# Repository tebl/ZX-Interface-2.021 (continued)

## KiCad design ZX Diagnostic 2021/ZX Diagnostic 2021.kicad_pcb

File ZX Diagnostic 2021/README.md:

# ZX Diagnostic 2.021
The *ZX Diagnostic 2.021*, simply referred to as the *diagnostic cartridge* for the remainder of this document, has been specially made to work with the [diagnostic firmware](https://github.com/brendanalford/zx-diagnostics) developed by Brendan Alford. Part of the hardware used within the *ZX Interface 2.021* has been designed to be functionally similar to other diagnostic cartridges, in particular the bank switching scheme and the way  the cartridge can be disabled by the computer was based on the following [blog post](https://blog.gjmccarthy.co.uk/wp-content/uploads/2019/12/how.html).

The rest of the functionality needed to serve as a diagnostic cartridge has been added to the *ZX Diagnostic 2.021*, apart from being a 16K cartridge there is an 8bit latch that will be used to output diagnostic status to the LEDs. The LEDs will allow some additional feedback to show that the computer is somewhat functional, even when there there is no image. Compared to the *ZX Cartridge 2.021*, this only supports a single ROM chip with sizes ranging ranging from 27C128 up to 27C512.

Note that there are various faceplates available for the cartridges, these complete the look of the cartridge as well as help them balance on top of the interface. Check out the [faceplates](https://github.com/tebl/ZX-Interface-2.021/tree/main/faceplates) section for an overview over the ones that have been made available, also see [PCBWay shared projects](https://www.pcbway.com/project/shareproject/?tag=ZX%20Interface%202.021).

- [1> Building the cartridge](#1-building-the-cartridge)
  - [1.1> Soldering it together](#11-soldering-it-together)
  - [1.2> Assembling the unit](#12-assembling-the-unit)
  - [1.3> Testing it out](#13-testing-it-out)
- [2> Schematic](#2-schematic)
- [3> BOM](#3-bom)

# 1> Building the cartridge
Building the unit assumes you have at least minor experience soldering things together, recommended is at least a soldering station with adjustable temperature to get started - usually you'll want some 60/40 solder tin (if you can get that where you live). Given that we're going to be flashing data onto EPROM chips, you'll need an EPROM programmer suitable for this task - the one I'm using is a MiniPro TL866CS and so far it's surpassed my expectations for such a reasonably priced device. If you are going to use EPROM chips you will need an EPROM ereaser as well, but read on - you might not need that depending on the chips you purchase.

With the equipment sorted, now comes the shopping - so head on over to the [BOM](#3-bom)-section for some information on what you need. Note that with sites such as ebay, AliExpress and similar sites that sell cheap chinese components, you'll need to treat these as a suggested search term and look for something that matches the gallery pictures.

You'll need to order some EPROM chips as well. As previously mentioned, you can use anything from 27C128 up to 27C512 chips. One specific chip I can recommend looking for is the W27C512 chip as that is actually an EEPROM with the same pin layout, meaning you won't need the previously mentioned EPROM ereaser. The price difference is negligible unless you're going to make a lot of them.

## 1.1> Soldering it together
The construction of this unit should be fairly straight-forward, just take your time in order to make sure everything goes into place - more or less straight. I usually recommend starting by having a good look at the PCBs, try to figure out where all of the listed components go and in which orientation they go (all of this should be clearly marked on the silkscreen). 

The last version I built is the one shown above, and going forward I usually try installing components sorted by physical - going from the smallest to the largest. The reason for this is that you want to be able to solder most of it into place before it starts wobbling on your desk, for the *ZX Diagnostic 2.021* this means saving all of those LEDs until last.

At this point we've soldered in all of the resistors, but take note that one of them will have a different resistor value from the others. There are two solder jumpers on the cartridge, these are clearly labelled A14 and A15 with pin 1 identifiable as the square pad. You need to add some solder to bridge between two of the pins, this is dependent on the type of (E)EPROM you are going to install into the socket marked U1 - see the table below for all supported ROM types.

| (E)EPROM | A15 | A14 |
| -------- | --- | --- |
| 27C512   | 1-2 | 1-2 |     
| 27C256   | 2-3 | 1-2 |     
| 27C128   | 2-3 | 2-3 |

Next is the single right-angle pin header that is used to enable the LEDs at the top - to get that on straight, just solder on one of the pins, then reheat and adjust the position before soldering in the final pin. Alternatively you could also just solder a wire across the two pins to keep them permanently disabled, but this isn't recommended unless you know that the cartridge will only ever be used for diagnostic purposes.

At this point, we've just gone ahead and added both the sockets, making sure to match the indent in the sockets with the symbols on the silkscreen - this means that pin 1 of the ICs is at the top-right corner of the sockets. Solder in the corners of the sockets first, gently reheat one pin at a time and press the socket firmly against board to avoid accidentally soldering it in at an angle (removing a socket is a lot harder than it is to solder it in).

The ceramic capacitors do not have a polarity, so we can just solder them into place without issues. Personally I tend to ensure that the values printed on them is visible from the outside, but that's just nit-picking.

The last thing we're going to solder into place is the LEDs, but as they need to line up with the holes in the faceplate we'll need to take care when doing so to ensure that they're straight. Before we get that far though, we'll need to say a few words about the LEDs themselves - soldering them in the wrong way will ensure that won't work. I can never remember what the proper names of each of the pins are, so I'll just pass along the way I do it - essentially the longest lead goes into the round hole. The shorter lead, big surprise here, goes into the other hole.

Just do one row at a time, soldering in just one of the pins - then reheat and push the LED flush against the board (no matter how hard I try, they're never straight enough on the first try). When you're sure that all of them line up correctly, only then do you solder in the other pin.

The last step that we need to do is simply inserting the chips, as has been pictured so far I've soldered the jumpers according to the settings for a 27C512-type of ROM - in this case using the W27C512 EEPROM. Make sure that you insert the chips in the correct orientation, the indent will be to the right. I put together a separate document that goes into [flashing the (E)EROMs](https://github.com/tebl/ZX-Interface-2.021/blob/main/documentation/flash_eeprom.md), the diagnostic firmware can be downloaded from the authors [github](https://github.com/brendanalford/zx-diagnostics/releases)-repository (it'll be called *testrom.bin*, this file can only be downloaded as part of the releases). Then add a jumper cap to enable the LEDs.

## 1.2> Assembling the unit
There isn't all that much that can be said for assembling the unit, chances are you've already finished the entire thing by this point. The only remaining step would just be to add a [faceplate](https://github.com/tebl/ZX-Interface-2.021/tree/main/faceplates), it helps keep the cartridge from flopping around in the cartridge slot while also adding quite a bit of visual flair to it.

The faceplate is just a simple PCB, the suggested way of attaching it is by using components found in cheap *M3 nylon hex* kits. It will look at its best when using an 8mm nylon hex standoff (F-F), then adding screws from both sides. If, on the other hand, you want to stay within the kit - then I suggest using the 8mm M-F standoffs, add M3 nuts on the bottom and snip off the remaining part of the nylon screw that'll poke through. Add screws on top. Your success on this step will be dependent on how straight you soldered on the LEDs, so reheat and adjust any that fails to line up with the holes in the faceplate.

## 1.3> Testing it out
I shouldn't have to say it at this point, but I'll do so anyway - cartridges are not memory cards, plugging them in or unplugging them while the system is powered on will **KILL** your equipment. With that out of the way, just plug the cartridge into the slot and then apply power to see if whatever you put into the first 16K of the (E)EPROM starts up as expected. I put together a separate document that goes into [flashing the (E)EROMs](https://github.com/tebl/ZX-Interface-2.021/blob/main/documentation/flash_eeprom.md).

The ZX Spectrum doesn't actually have any knowledge of any of the bank switching logic installed on the interface, in fact the ROM in your computer will be completely disabled when any cartridge is inserted into the interface. Given that this is meant to be a diagnostic cartridge, I'll assume you've gone ahead and used Brendan Alfords diagnostic firmware as the first 16K bank - it should start automatically and run through the tests as it should.

Unless you hold down any of the buttons when starting the computer, it should run through all of the tests once and then - after a countdown - page out the diagnostic ROM and return you to the standard ZX Spectrums basic. This is normal, it just shows that the entire system for the most part works as it should. At this point you might want to try out any of the images put into the other ROM banks, I've added some more details on what to do next to the [bank_switching](https://github.com/tebl/ZX-Interface-2.021/blob/main/documentation/bank_switching.md) document.

You can control the LEDs directly from basic if you want to, they're placed on port 63 and by using the *OUT* command you can control them. All you need to do is write a value to have the LEDs display it in binary, for example the following to separately light up each row of LEDs:
```
OUT 63, 85
OUT 63, 170
```

You know you want to program an LED chaser now, you know you do! In case you're not old enough, they're what made KITT cool and the Cylons scary.

# 2> Schematic
The supplied KiCad files should be sufficient as both a schematic and as a  starting point for ordering PCBs (basically you could just zip the contents of the export folder and upload that on a fabrication site), the schematic is also available in [PDF-format](https://github.com/tebl/ZX-Interface-2.021/tree/main/documentation/schematic) and this is what you'll need to print and work your way through this things don't work as expected after assembly.

# 3> BOM
Most parts should be easy to get a hold of from your favourite local electronic component shop, but given that I don't have access to such shops where I live so everything was based on whatever I could get cheapest from eBay/AliExpress (free shipping, but plan on waiting 3-4 weeks for delivery). Components in parenthesis can be considered optional to enable basic functionality, but where's the fun in that? You deserve the complete package.

| Reference             | Item                                                              | Count | Order  |
| --------------------- | ----------------------------------------------------------------- | ----- | ------ |
| Cartridge PCB         | Fabricate using Gerber files                                      |     1 | [PCBWay](https://www.pcbway.com/project/shareproject/ZX_Diagnostic_2_021.html)
| Faceplate PCB *       | Fabricate using Gerber files                                      |    (1)| [PCBWay](https://www.pcbway.com/project/shareproject/ZX_Diagnostic_2_021__Faceplate_FA1_.html)
| JP1 **                | 2pin right-angle pin-header (with jumper cap)                     |    (1)|
| U1                    | 27C128,27C256 or 27C512 (W27C512 recommended)                     |     1 |
| U2 **                 | 74HCT374 (DIP-20)                                                 |    (1)|
| C1                    | 100nF ceramic capacitor (5mm pin spacing)                         |     1 |
| C2 **                 | 100nF ceramic capacitor (5mm pin spacing)                         |    (1)|
| R1-R8 **              | 330 ohm resistor                                                  |    (8)|
| R9 **                 | 10k ohm resistor                                                  |     1 |
| Mounting *            | Nylon M3 hex standoffs 8mm                                        |    (4)|
| Mounting *            | Nylon M3x6mm nylon screws                                         |    (4)|
| Mounting *            | M3 nylon nut                                                      |    (4)|  

*) The easiest way of ordering these is to just one of the M3 nylon standoff kits on ebay, AliExpress or any similar sites. That way you'll get more than what you need in various sizes for future projects as well. Check out [faceplate](https://github.com/tebl/ZX-Interface-2.021/tree/main/faceplates) section of this repository or [PCBWay shared projects](https://www.pcbway.com/project/shareproject/?tag=ZX%20Interface%202.021) for available options.

**) These components are used for the LED output, they can be considered optional for building a simple cartridge though they're recommended when you want to use it for diagnostic purposes.

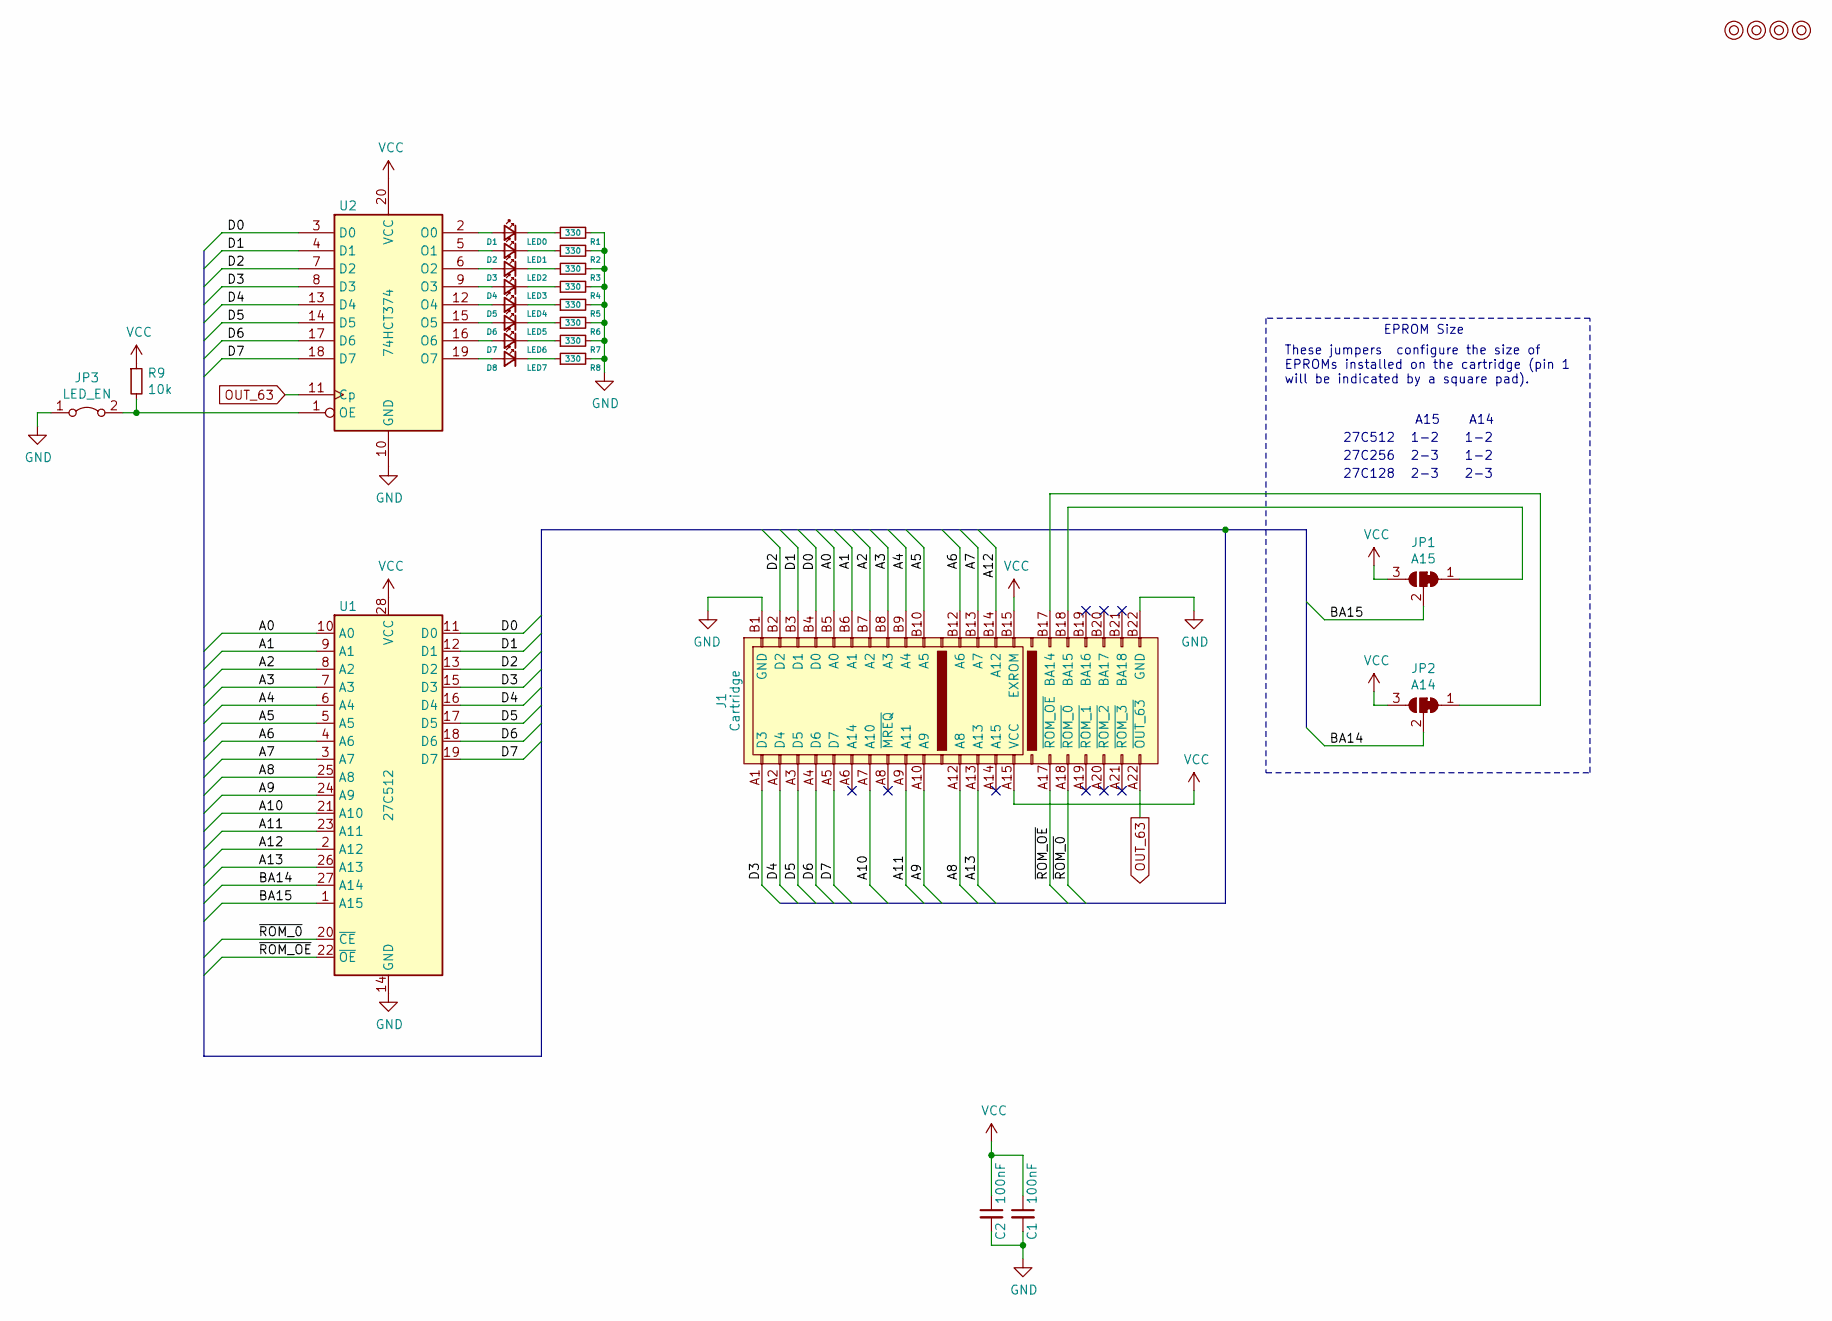
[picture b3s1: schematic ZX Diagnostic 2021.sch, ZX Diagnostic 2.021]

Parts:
C1, C2: 100nF; C_Disc_D4.7mm_W2.5mm_P5.00mm
D1: LED0; LED_D5.0mm
D2: LED1; LED_D5.0mm
D3: LED2; LED_D5.0mm
D4: LED3; LED_D5.0mm
D5: LED4; LED_D5.0mm
D6: LED5; LED_D5.0mm
D7: LED6; LED_D5.0mm
D8: LED7; LED_D5.0mm
J1: Cartridge; ZX_Spectrum_Cartridge
JP1: A15; select
JP2: A14; select
JP3: LED_EN; PinHeader_1x02_P2.54mm_Horizontal
M1, M2, M3, M4: Mounting; M3_pin
R1, R2, R3, R4, R5, R6, R7, R8: 330; R_Axial_DIN0207_L6.3mm_D2.5mm_P10.16mm_Horizontal
R9: 10k; R_Axial_DIN0207_L6.3mm_D2.5mm_P10.16mm_Horizontal
U1: 27C512; DIP-28_W15.24mm_Socket_LongPads
U2: 74HCT374; DIP-20_W7.62mm_Socket_LongPads

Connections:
/A0: J1.B5 (A0), U1.10 (A0)
/A1: J1.B6 (A1), U1.9 (A1)
/A2: J1.B7 (A2), U1.8 (A2)
/A3: J1.B8 (A3), U1.7 (A3)
/A4: J1.B9 (A4), U1.6 (A4)
/A5: J1.B10 (A5), U1.5 (A5)
/A6: J1.B12 (A6), U1.4 (A6)
/A7: J1.B13 (A7), U1.3 (A7)
/A8: J1.A12 (A8), U1.25 (A8)
/A9: J1.A10 (A9), U1.24 (A9)
/A10: J1.A7 (A10), U1.21 (A10)
/A11: J1.A9 (A11), U1.23 (A11)
/A12: J1.B14 (A12), U1.2 (A12)
/A13: J1.A13, U1.26 (A13)
/BA14: JP2.2 (C), U1.27 (A14)
/BA15: JP1.2 (C), U1.1 (A15)
/D0: J1.B4 (D0), U1.11 (D0), U2.3 (D0)
/D1: J1.B3 (D1), U1.12 (D1), U2.4 (D1)
/D2: J1.B2 (D2), U1.13 (D2), U2.7 (D2)
/D3: J1.A1 (D3), U1.15 (D3), U2.8 (D3)
/D4: J1.A2 (D4), U1.16 (D4), U2.13 (D4)
/D5: J1.A3 (D5), U1.17 (D5), U2.14 (D5)
/D6: J1.A4 (D6), U1.18 (D6), U2.17 (D6)
/D7: J1.A5 (D7), U1.19 (D7), U2.18 (D7)
/~ROM_0: J1.A18 (~ROM_0), U1.20 (~CE)
/~ROM_OE: J1.A17 (~ROM_OE), U1.22 (~OE)
GND: C1.2, C2.2, J1.B1 (GND), J1.B22 (GND), JP3.1 (A), R1.2, R2.2, R3.2, R4.2, R5.2, R6.2, R7.2, R8.2, U1.14 (GND), U2.10 (GND)
unnamed: D1.1 (K), R1.1
unnamed: D1.2 (A), U2.2 (O0)
unnamed: D2.1 (K), R2.1
unnamed: D2.2 (A), U2.5 (O1)
unnamed: D3.1 (K), R3.1
unnamed: D3.2 (A), U2.6 (O2)
unnamed: D4.1 (K), R4.1
unnamed: D4.2 (A), U2.9 (O3)
unnamed: D5.1 (K), R5.1
unnamed: D5.2 (A), U2.12 (O4)
unnamed: D6.1 (K), R6.1
unnamed: D6.2 (A), U2.15 (O5)
unnamed: D7.1 (K), R7.1
unnamed: D7.2 (A), U2.16 (O6)
unnamed: D8.1 (K), R8.1
unnamed: D8.2 (A), U2.19 (O7)
unnamed: J1.B17 (BA14), JP2.1 (A)
unnamed: J1.B18 (BA15), JP1.1 (A)
unnamed: JP3.2 (B), R9.2, U2.1 (OE)
OUT_63: J1.A22 (~OUT_63), U2.11 (Cp)
VCC: C1.1, C2.1, J1.A15 (VCC), J1.B15 (EXROM), JP1.3 (B), JP2.3 (B), R9.1, U1.28 (VCC), U2.20 (VCC)

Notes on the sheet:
EPROM Size
These jumpers configure the size of EPROMs installed on the cartridge (pin 1 will be indicated by a square pad).
A15
A14
27C512
27C256
27C128
1-2
2-3

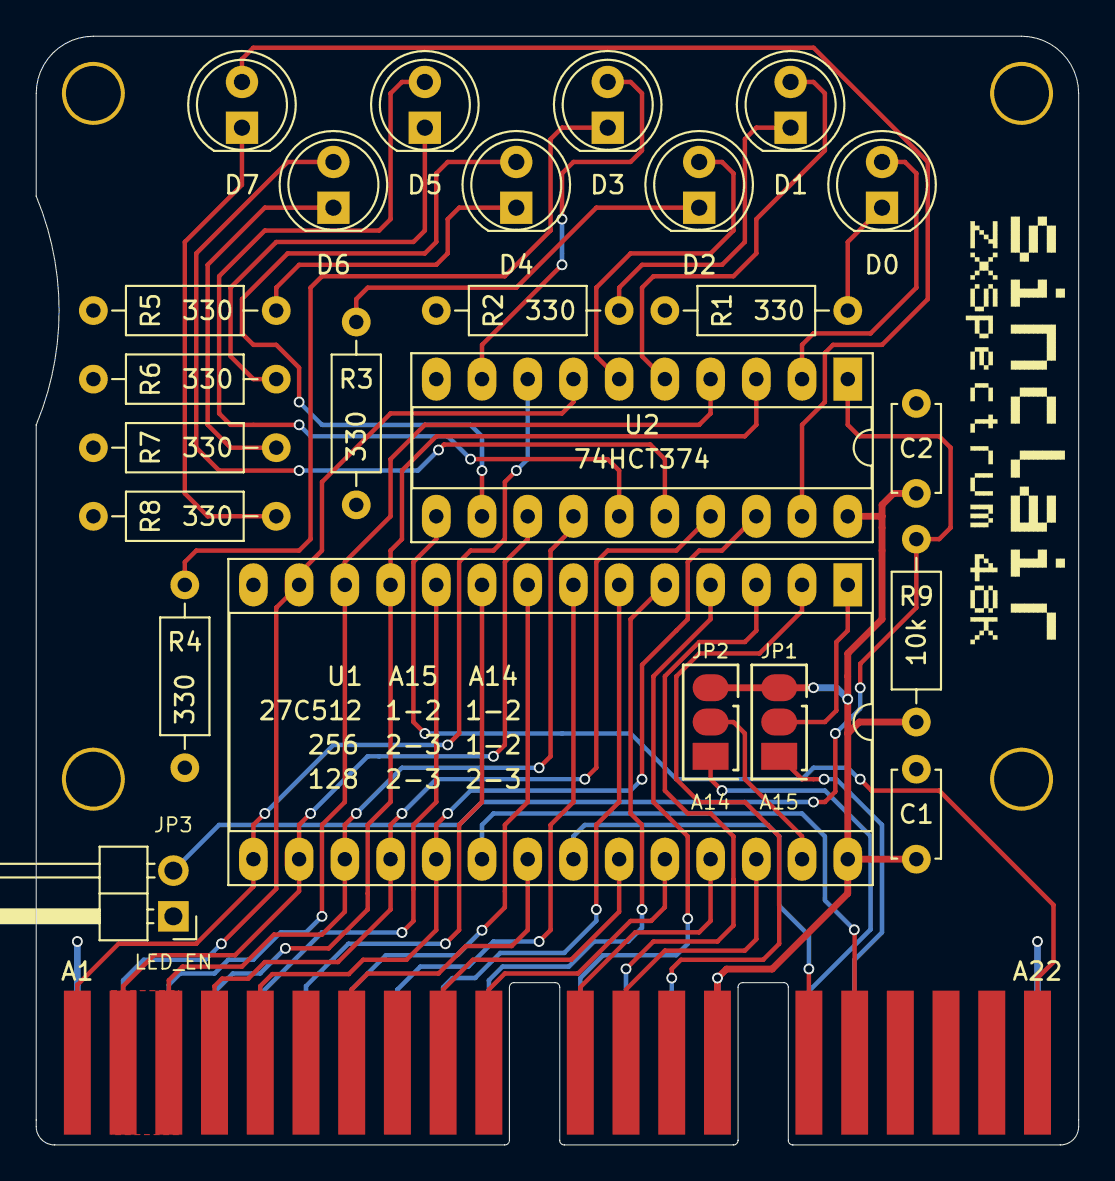
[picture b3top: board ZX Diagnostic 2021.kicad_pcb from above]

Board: 2 copper layers, 57.9 x 61.6 mm, 30 parts (0 on the bottom side), 48 nets.

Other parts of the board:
sinclair_title: sinclair_title

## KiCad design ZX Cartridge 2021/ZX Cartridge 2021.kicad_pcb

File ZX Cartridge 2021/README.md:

# ZX Cartridge 2.021
The ZX Cartridge 2.021, simply referred to as *cartridge* for the remainder of this document, is a modified version of the one released by Sinclair back in 1983. The original cartridge design was limited to 16K without any of the signals required to easily build a larger one, so the *ZX Cartridge 2.01* set out to fix that - simply by extending the length of the cartridge. This does mean that you can't use it with the original *Sinclair ZX Interface 2*, you can only use it with the *ZX Interface 2.021*.

Though the interface itself is able to address ROM chips in sizes up to 512K, four of them actually, the cartridge itself was designed with the ROM chips ranging from 27C128 up to 27C512. I might make a monster cartridge at some point, but given that there were only around 10 cartridges released for the original system - having the space for 8 of them is a good starting point.

Note that there are various faceplates available for the cartridges, these complete the look of the cartridge as well as help them balance on top of the interface. Check out the [faceplates](https://github.com/tebl/ZX-Interface-2.021/tree/main/faceplates) section for an overview over the ones that have been made available, also see [PCBWay shared projects](https://www.pcbway.com/project/shareproject/?tag=ZX%20Interface%202.021).

- [1> Building the cartridge](#1-building-the-cartridge)
  - [1.1> Soldering it together](#11-soldering-it-together)
  - [1.2> Assembling the unit](#12-assembling-the-unit)
  - [1.3> Testing it out](#13-testing-it-out)
- [2> Schematic](#2-schematic)
- [3> BOM](#3-bom)

# 1> Building the cartridge
Building the unit assumes you have at least minor experience soldering things together, recommended is at least a soldering station with adjustable temperature to get started - usually you'll want some 60/40 solder tin (if you can get that where you live). Given that we're going to be flashing data onto EPROM chips, you'll need an EPROM programmer suitable for this task - the one I'm using is a MiniPro TL866CS and so far it's surpassed my expectations for such a reasonably priced device. If you are going to use EPROM chips you will need an EPROM ereaser as well, but read on - you might not need that depending on the chips you purchase.

With the equipment sorted, now comes the shopping - so head on over to the [BOM](#3-bom)-section for some information on what you need. Note that with sites such as ebay, AliExpress and similar sites that sell cheap chinese components, you'll need to treat these as a suggested search term and look for something that matches the gallery pictures.

You'll need to order some EPROM chips as well. As previously mentioned, you can use anything from 27C128 up to 27C512 chips. One specific chip I can recommend looking for is the W27C512 chip as that is actually an EEPROM with the same pin layout, meaning you won't need the previously mentioned EPROM ereaser. The price difference is negligible unless you're going to make a lot of them.

## 1.1> Soldering it together
The construction of this unit should be straight-forward, specifically as there are only a handful of components to deal with. If you are only going to install a single (E)EPROM into the board, you just need to solder in the left socket and the capacitor next to it.

There are two solder jumpers on the right side of the cartridge, these are clearly labelled A14 and A15 with pin 1 identifiable as the square pad. You need to add some solder to bridge between two of the pins, this is dependent on the type of (E)EPROM you are going to install into the slots (they need to be of the same kind so no mixing and matching).

| (E)EPROM | A15 | A14 |
| -------- | --- | --- |
| 27C512   | 1-2 | 1-2 |     
| 27C256   | 2-3 | 1-2 |     
| 27C128   | 2-3 | 2-3 |     

A completed unit with the jumpers soldered in for the installed 27C512 chip can be seen below, this is mainly all there is to it. The rest of the components that are usually associated with ZX Spectrum cartridges are integrated into the *ZX Interface 2.021* instead - meaning you can quickly solder together all the cartridges you'll ever need in just a few minutes.

## 1.2> Assembling the unit
There isn't all that much that can be said for assembling the unit, chances are you've already finished the entire thing by this point. The only remaining step would just be to add a [faceplate](https://github.com/tebl/ZX-Interface-2.021/tree/main/faceplates), it helps keep the cartridge from flopping around in the cartridge slot while adding quite a bit of visual flair to it.

The faceplate is just a simple PCB, the suggested way of attaching it is by using components found in cheap *M3 nylon hex* kits. It will look at its best when using an 8mm nylon hex standoff (F-F), then adding screws from both sides. If, on the other hand, you want to stay within the kit - then I suggest using the 8mm M-F standoffs, add M3 nuts on the bottom and snip off the remaining part of the nylon screw that'll poke through. Add screws on top.

## 1.3> Testing it out
I shouldn't have to say it at this point, but I'll do so anyway - cartridges are not memory cards, plugging them in or unplugging them while the system is powered on will **KILL** your equipment. With that out of the way, just plug the cartridge into the slot and then apply power to see if whatever you put into the first 16K of the (E)EPROM starts up as expected.

The ZX Spectrum doesn't actually have any knowledge of any of the bank switching logic installed on the interface, in fact the ROM in your computer will be completely disabled when any cartridge is inserted into the interface. So in order to access any of the other banks available we'll need to come up with something else, but that is described separately in [bank_switching](https://github.com/tebl/ZX-Interface-2.021/blob/main/documentation/bank_switching.md) that have been included as part of the [documentation](https://github.com/tebl/ZX-Interface-2.021/tree/main/documentation).

# 2> Schematic
The supplied KiCad files should be sufficient as both a schematic and as a  starting point for ordering PCBs (basically you could just zip the contents of the export folder and upload that on a fabrication site), the schematic is also available in [PDF-format](https://github.com/tebl/ZX-Interface-2.021/tree/main/documentation/schematic) and this is what you'll need to print and work your way through this things don't work as expected after assembly.

# 3> BOM
Most parts should be easy to get a hold of from your favourite local electronic component shop, but given that I don't have access to such shops where I live so everything was based on whatever I could get cheapest from eBay/AliExpress (free shipping, but plan on waiting 3-4 weeks for delivery). 

| Reference             | Item                                                              | Count | Order  |
| --------------------- | ----------------------------------------------------------------- | ----- | ------ |
| Cartridge PCB         | Fabricate using Gerber files                                      |     1 | [PCBWay](https://www.pcbway.com/project/shareproject/ZX_Cartridge_2_021.html)
| Faceplate PCB *       | Fabricate using Gerber files                                      |    (1)| [PCBWay](https://www.pcbway.com/project/shareproject/ZX_Cartridge_2_021__Faceplate_FA1_.html)
| U1,U2 **              | 27C128,27C256 or 27C512 (W27C512 recommended)                     |  1 (1)|
| C1,C2 **              | 100nF ceramic capacitor (5mm pin spacing)                         |  1 (1)|
| Mounting *            | Nylon M3 hex standoffs 8mm                                        |    (4)|
| Mounting *            | Nylon M3x6mm nylon screws                                         |    (4)|
| Mounting *            | M3 nylon nut                                                      |    (4)|  

*) The easiest way of ordering these is to just one of the M3 nylon standoff kits on ebay, AliExpress or any similar sites. That way you'll get more than what you need in various sizes for future projects as well. Check out [faceplate](https://github.com/tebl/ZX-Interface-2.021/tree/main/faceplates) section of this repository or [PCBWay shared projects](https://www.pcbway.com/project/shareproject/?tag=ZX%20Interface%202.021) for available options.

**) Only a single (E)EPROM is required to build a cartridge, components U2 and C2 are therefore listed as optional. Installing 28-pin wide DIP sockets is highly recommended rather than soldering the (E)EPROM directly to the board.

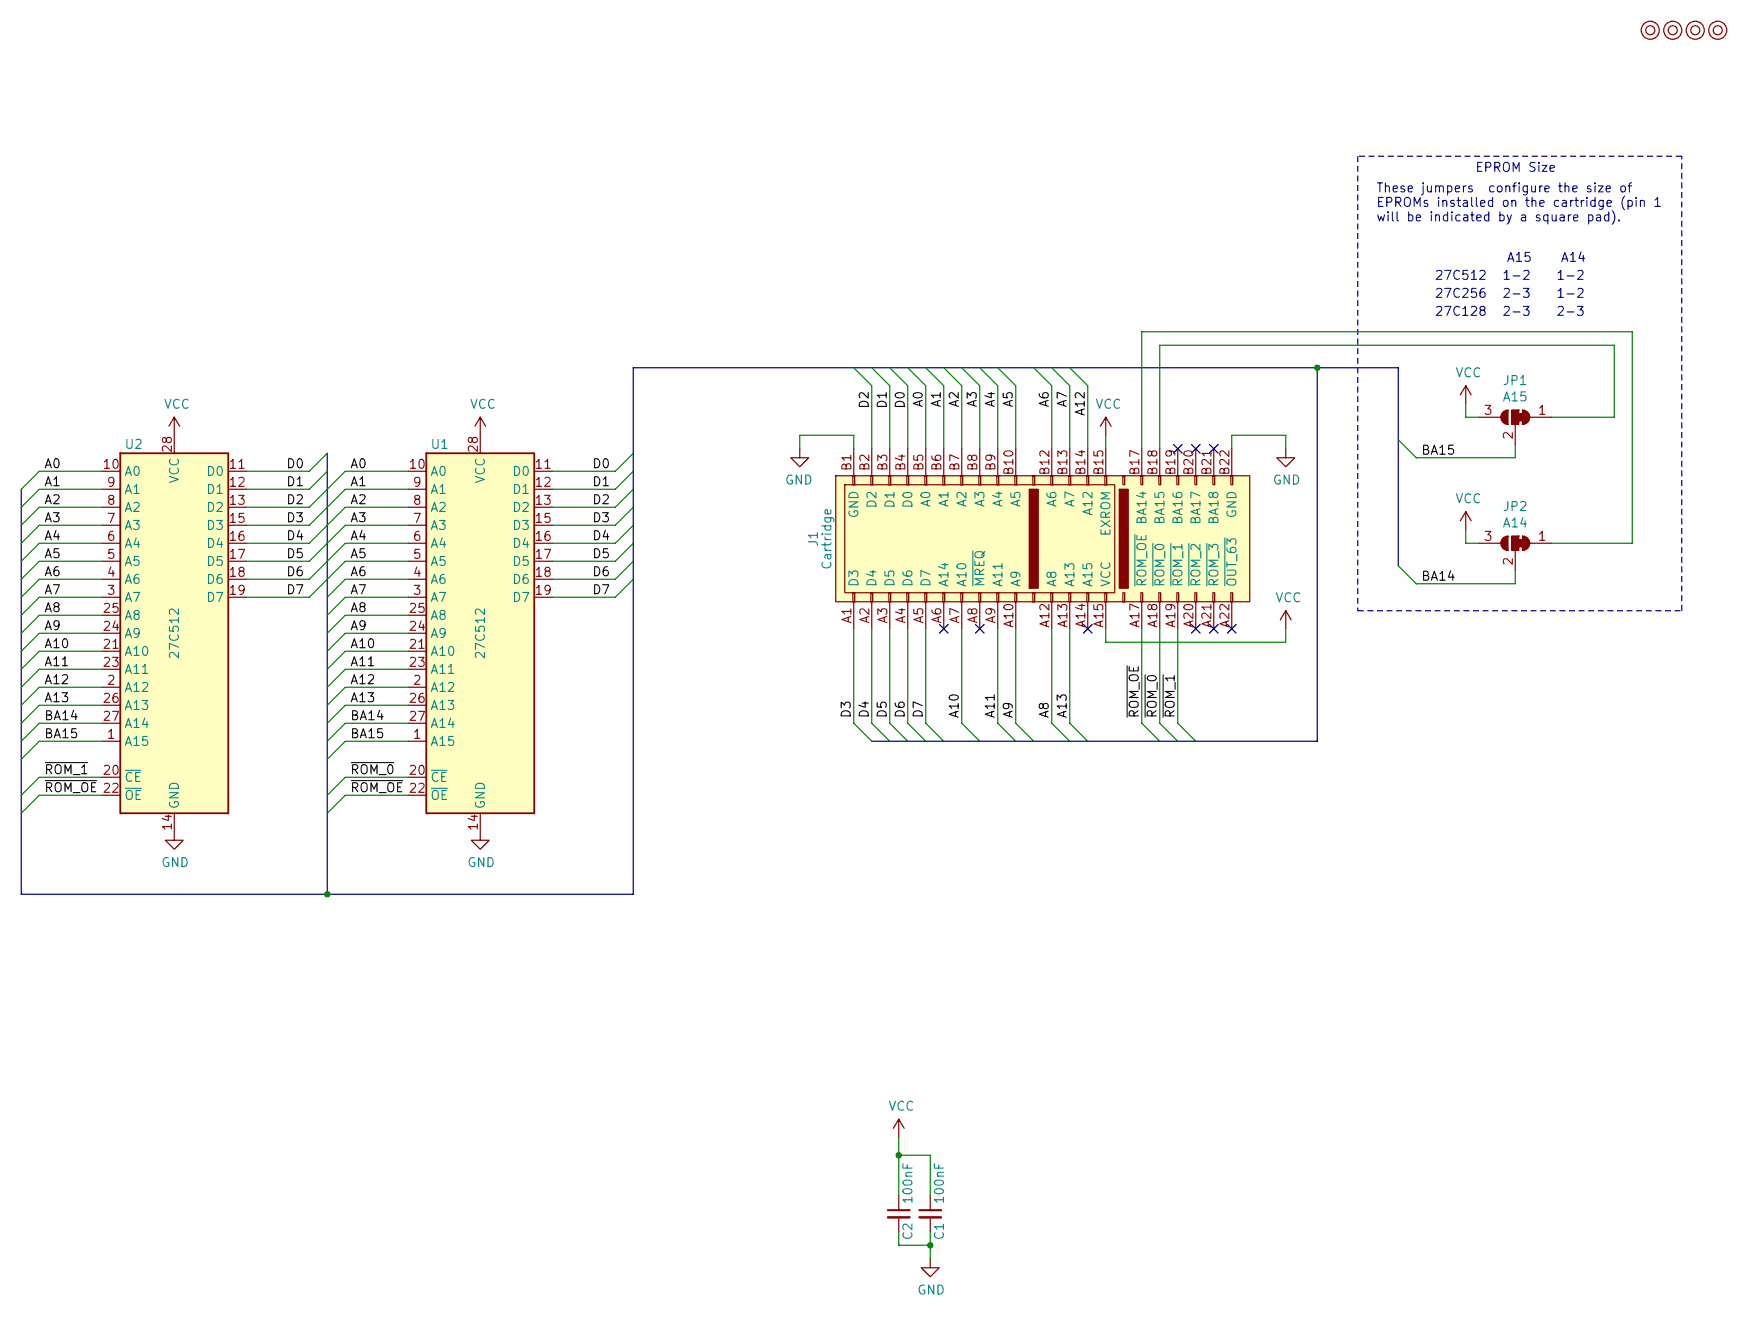
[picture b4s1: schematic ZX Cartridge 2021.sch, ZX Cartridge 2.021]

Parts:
C1, C2: 100nF; C_Disc_D4.7mm_W2.5mm_P5.00mm
J1: Cartridge; ZX_Spectrum_Cartridge
JP1: A15; select
JP2: A14; select
M1, M2, M3, M4: Mounting; M3_pin
U1, U2: 27C512; DIP-28_W15.24mm_Socket_LongPads

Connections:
/A0: J1.B5 (A0), U1.10 (A0), U2.10 (A0)
/A1: J1.B6 (A1), U1.9 (A1), U2.9 (A1)
/A2: J1.B7 (A2), U1.8 (A2), U2.8 (A2)
/A3: J1.B8 (A3), U1.7 (A3), U2.7 (A3)
/A4: J1.B9 (A4), U1.6 (A4), U2.6 (A4)
/A5: J1.B10 (A5), U1.5 (A5), U2.5 (A5)
/A6: J1.B12 (A6), U1.4 (A6), U2.4 (A6)
/A7: J1.B13 (A7), U1.3 (A7), U2.3 (A7)
/A8: J1.A12 (A8), U1.25 (A8), U2.25 (A8)
/A9: J1.A10 (A9), U1.24 (A9), U2.24 (A9)
/A10: J1.A7 (A10), U1.21 (A10), U2.21 (A10)
/A11: J1.A9 (A11), U1.23 (A11), U2.23 (A11)
/A12: J1.B14 (A12), U1.2 (A12), U2.2 (A12)
/A13: J1.A13, U1.26 (A13), U2.26 (A13)
/BA14: JP2.2 (C), U1.27 (A14), U2.27 (A14)
/BA15: JP1.2 (C), U1.1 (A15), U2.1 (A15)
/D0: J1.B4 (D0), U1.11 (D0), U2.11 (D0)
/D1: J1.B3 (D1), U1.12 (D1), U2.12 (D1)
/D2: J1.B2 (D2), U1.13 (D2), U2.13 (D2)
/D3: J1.A1 (D3), U1.15 (D3), U2.15 (D3)
/D4: J1.A2 (D4), U1.16 (D4), U2.16 (D4)
/D5: J1.A3 (D5), U1.17 (D5), U2.17 (D5)
/D6: J1.A4 (D6), U1.18 (D6), U2.18 (D6)
/D7: J1.A5 (D7), U1.19 (D7), U2.19 (D7)
/~ROM_0: J1.A18 (~ROM_0), U1.20 (~CE)
/~ROM_1: J1.A19 (~ROM_1), U2.20 (~CE)
/~ROM_OE: J1.A17 (~ROM_OE), U1.22 (~OE), U2.22 (~OE)
GND: C1.2, C2.2, J1.B1 (GND), J1.B22 (GND), U1.14 (GND), U2.14 (GND)
unnamed: J1.B17 (BA14), JP2.1 (A)
unnamed: J1.B18 (BA15), JP1.1 (A)
VCC: C1.1, C2.1, J1.A15 (VCC), J1.B15 (EXROM), JP1.3 (B), JP2.3 (B), U1.28 (VCC), U2.28 (VCC)

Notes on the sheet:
EPROM Size
These jumpers configure the size of EPROMs installed on the cartridge (pin 1 will be indicated by a square pad).
A15
A14
27C512
27C256
27C128
1-2
2-3

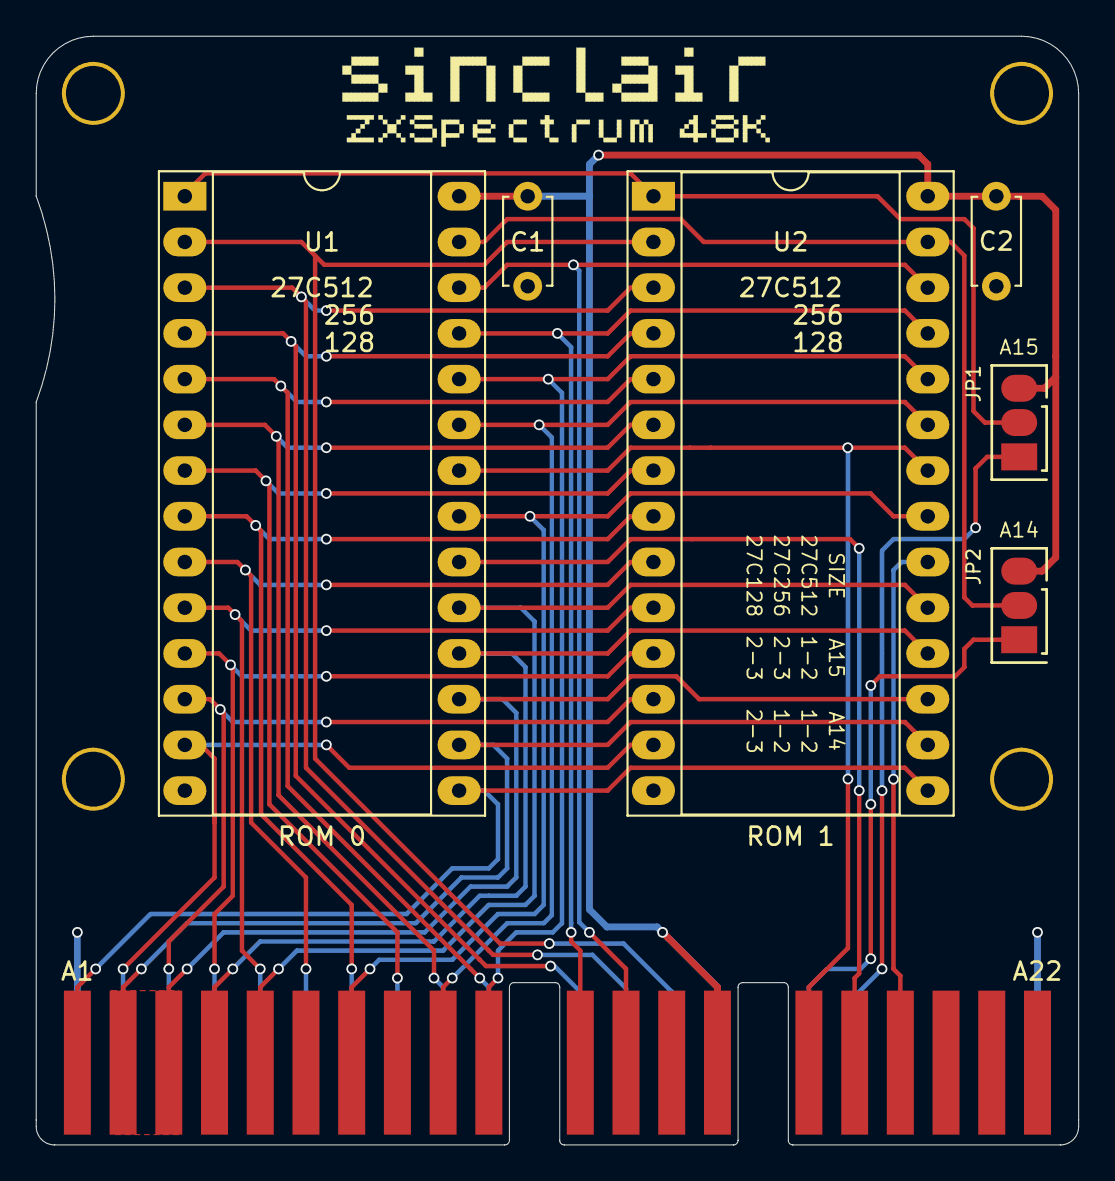
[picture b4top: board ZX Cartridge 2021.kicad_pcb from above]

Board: 2 copper layers, 57.9 x 61.6 mm, 13 parts (1 on the bottom side), 31 nets.

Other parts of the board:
sinclair_title: sinclair_title
sinclair_title#2: sinclair_title

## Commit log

2021-02-27 New project
2021-02-28 Rough sketch
2021-03-03 Created proper extended cartridge symbols
2021-03-03 Assigned footprints
2021-03-04 Laying some tracks...
2021-03-05 ... and the rest
2021-03-05 Added some artwork
2021-03-05 Silkscreen tweaks
2021-03-05 Preview
2021-03-05 Cartridge components thrown in
2021-03-05 27c512 cartridge layout done
2021-03-06 Added 27C256 and 27C128 compatibility
2021-03-06 Added grip
2021-03-06 Diagnostic riding the bus
2021-03-06 Diagnostic layout done
2021-03-07 Gerber export
2021-03-07 Unit Faceplate added
2021-03-08 Diagnostic faceplate
2021-03-08 Added blank faceplate
2021-03-21 Cartridge pins were mirrored, still need to change cartridges
2021-03-23 Made 74ls245 open collector instead of using resistors
2021-03-23 Cleanup
2021-03-23 unscrambled joystick pins
2021-03-23 Tweaked interface title
2021-03-23 Add POWER LED cutout
2021-03-23 Fixed cartridge pinout
2021-03-23 Fixed diagnostic pinout
2021-03-23 Fixed a mounting pin bug
2021-03-31 Added empty cartridge module for offline artwork
2021-04-02 Added build images
2021-04-02 Larger DB9 cutouts
2021-04-05 Untested 1983 cartridge (16k only)
2021-04-05 Changed datasheet to match chip actually used
2021-04-06 Changed 1983 to 1.983
2021-04-06 Placeholder
2021-04-06 Main README added
2021-04-06 Added hot-swap warning
2021-04-09 bank switching document
2021-04-09 Cartridge 2.021 README
2021-04-09 Fixed wording
2021-04-09 Added eeprom programming instructions
2021-04-09 Added diagnostic README
2021-04-09 LED out notice
2021-04-10 Added image
2021-04-10 Marked positive C5 pin
2021-04-10 Interface README contents
2021-04-10 Fixed typos
2021-04-11 Tabled module overview
2021-04-11 Updated order URLs
2021-04-14 Added some images
2021-04-16 Tweaked edge shape
2021-04-23 Added z80 loader for bank switching
2021-04-23 Renamed loader directory
2021-04-23 Added cartridge creator
2021-04-23 Add NMI handler
2021-04-23 Remove commented out code
2021-04-23 Removed todo item
2021-04-23 Moved fonts into a separate directory
2021-04-23 Can now replace fonts
2021-04-23 Made joystick work better in menu
2021-04-23 Font README
2021-04-24 Fixed code initialization problem by actually initializing stack
2021-04-24 Added a blank slot placeholder
2021-04-24 Fixed issue with font replacement
2021-04-24 Added Intel HEX converter
2021-04-24 Support HEX file for files larger than 64K
2021-04-24 Change hex formatting
2021-04-24 Return correct size
2021-04-25 Basic cartridge
2021-04-25 Added images
2021-04-25 Updated bank switching documentation
2021-04-25 Updated document
2021-04-25 Update main README
2021-04-25 Cartridge loader README
2021-04-25 Added references
2021-04-25 cartridge_creator README
2021-04-25 Added index
2021-04-25 Fixed typo
2021-04-27 Read joystick 2 as well
2021-04-27 Updated schematic
2021-04-27 Cassette themed faceplate
2021-04-27 Larger writable area
2021-04-27 Moved pins to line up with original Kempson Pro Joystick interface
2021-04-27 Cartridge 1.983 build images
2021-04-28 Cartridge creator support blank slots
2021-04-28 Updated loader
2021-04-29 Changed FA1 design
2021-04-29 ZX Cartridge 1.983 images
2021-05-03 snapshot_loader, first attempt
2021-05-03 Create cartridge from snapshot
2021-05-03 Generate last stand routines on the fly
2021-05-03 Can override loader address
2021-05-03 Verify basic LoaderAddress sanity
2021-05-04 Ignore file
2021-05-04 Snapshot placeholder
2021-05-04 Add file
2021-05-04 Updated README with snapshot details
2021-05-04 Snapshot loader README
2021-05-04 Typo
2021-05-04 More typoes
2021-05-04 Add images
2021-05-05 Moved text and border attributes into ROM
2021-05-06 Creator can specify text attributes
2021-05-06 Typos
2021-05-07 Add FAQ
2021-05-07 Added some text
2021-05-09 Marked pinouts for smaller chips
2021-05-09 Updated basic cartridge
2021-05-09 Add image
2021-05-09 Faceplate README
2021-05-10 Cartridge 1.983 README
2021-08-26 Cartridge 1.983 needed some more height to clear RAM turbo interface case
2021-09-12 1.983 README updated
2024-11-21 Missing schematic
